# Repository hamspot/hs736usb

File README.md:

# Ham Spot Inc
##  HS-736USB
http://hamspot.com/33-prod-hs-736usb

### FT-736R to HRD USB Interface
The Yaesu FT-736R remains a popular satellite ground station transceiver.  However some modern computer software is not compatible with the CAT interface on the FT-736R.  Ham Radio Deluxe, in particular, does not support the FT-736R.  Ham Radio Deluxe does support the Yaesu FT-847 which has similar features.  We can solve this incompatibility by programming a CAT interface to present a FT-847 to the PC and emulate the new commands not supported on the FT-736R.  

Features not present on the FT-736R are ignored.  Memory channels are not supported and the radio must be set to VFO, also satellite mode must be set to VFO, before enabling CAT control of the radio.  1240 MHz is mapped to 240 MHz because the FT-847 does not have 4 MHz digits.

### Credits
A short history, archived Comcast pages, and the original downloads are in **[Archives/README.md](Archives/README.md)**.

The concept was developed by Dave, KA6BFB in 2010 (Windows VB proof of concept, virtual serial ports): [Archives/Software.md](Archives/Software.md).

The hardware version was developed by Chuck, N6BIL (PIC18F14K50, GPL source and Eagle CAD): [Archives/Hardware.md](Archives/Hardware.md).

Ham Spot Inc based the HS-736USB on their great work and thanks them immensely for their hard work on solving a challenging problem! The goal of Ham Spot Inc is that if this interface is popular we will develop similar interfaces for other older rigs which are also not supported by HRD. Specifically in mind are the FT-757GXII, FT-890 and various Icom and Kenwood radios. There will likely be firmware updates to this hardware available on the http://hamspot.com/ website in the future. If you have a PIC programmer the chip has been socketed to allow you to flash new firmware or easily replace the device. If not, there will be made available an inexpensive preprogrammed chip that you can plugin to upgrade the firmware or convert the FT-736USB to another model Yaesu rig as they become supported.

### Arduino / ATmega328P port

An Arduino Uno/Nano port of the CAT translator lives in **[Arduino/](Arduino/)**. It keeps the PIC 847↔736 mapping, adds native-736 passthrough (pin A1 or a CAT opcode), PTT/band GPIO, and an S-meter PWM. The PIC firmware in `Firmware/` is unchanged.

```
arduino-cli compile --fqbn arduino:avr:nano Arduino/firmware
cd Arduino && test/run_suite.sh
```

See `Arduino/README.md`, `Arduino/docs/WIRING.md`, and `Arduino/docs/PROTOCOLS.md`. Operating manuals for both the PIC cabinet and the Arduino port are in [`Manual/`](Manual/).

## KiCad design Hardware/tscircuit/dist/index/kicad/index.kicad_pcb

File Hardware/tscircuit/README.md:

# HS-736USB Nano carrier (tscircuit)

Arduino Nano plugs into `JP_L` / `JP_R`. This board is the I/O carrier
(CAT, PTT MOSFET, RCA sense, dialect jumper, LCD, band, PWM). The MCU
is not redrawn.

CAT DIN pin 6 (+13.8 V) is not connected. Power is Nano USB 5 V.

## CLI

IndianaDell installs tscircuit under `~/.local` (`bin/tsci` runs `node`
on `cli.mjs`). The npm shebang is bun, and node cannot load `.tsx`.

From this directory, use the project CLI with bun:

```bash
BUN=/tmp/bunpkg/node_modules/bun/bin/bun.exe
# npm install --prefix /tmp/bunpkg bun  (Linux binary is named bun.exe)

"$BUN" node_modules/tscircuit/cli.mjs check netlist
"$BUN" node_modules/tscircuit/cli.mjs check schematic-placement
"$BUN" node_modules/tscircuit/cli.mjs check placement
"$BUN" node_modules/tscircuit/cli.mjs build --pcb-svgs --schematic-svgs --kicad-project
"$BUN" node_modules/tscircuit/cli.mjs check shorts
inkscape dist/index/pcb.svg --export-type=png --export-filename=dist/index/pcb.png --export-dpi=1200
inkscape dist/index/schematic.svg --export-type=png --export-filename=dist/index/schematic.png --export-dpi=1200
```

Do not `tsci push` or order boards unless asked.

`<schematicsheet>` is omitted on purpose: with it, `kicad_sch` export
is a hierarchical stub (`main.kicad_sch` never written). Sections
still group the schematic.

Known warnings: builtin symbols missing `{REFDES}` text; SOD-123 has
no 3D model on the tscircuit CDN.

Outputs: `dist/index/pcb.png`, `dist/index/schematic.png`,
`dist/index/kicad/`.

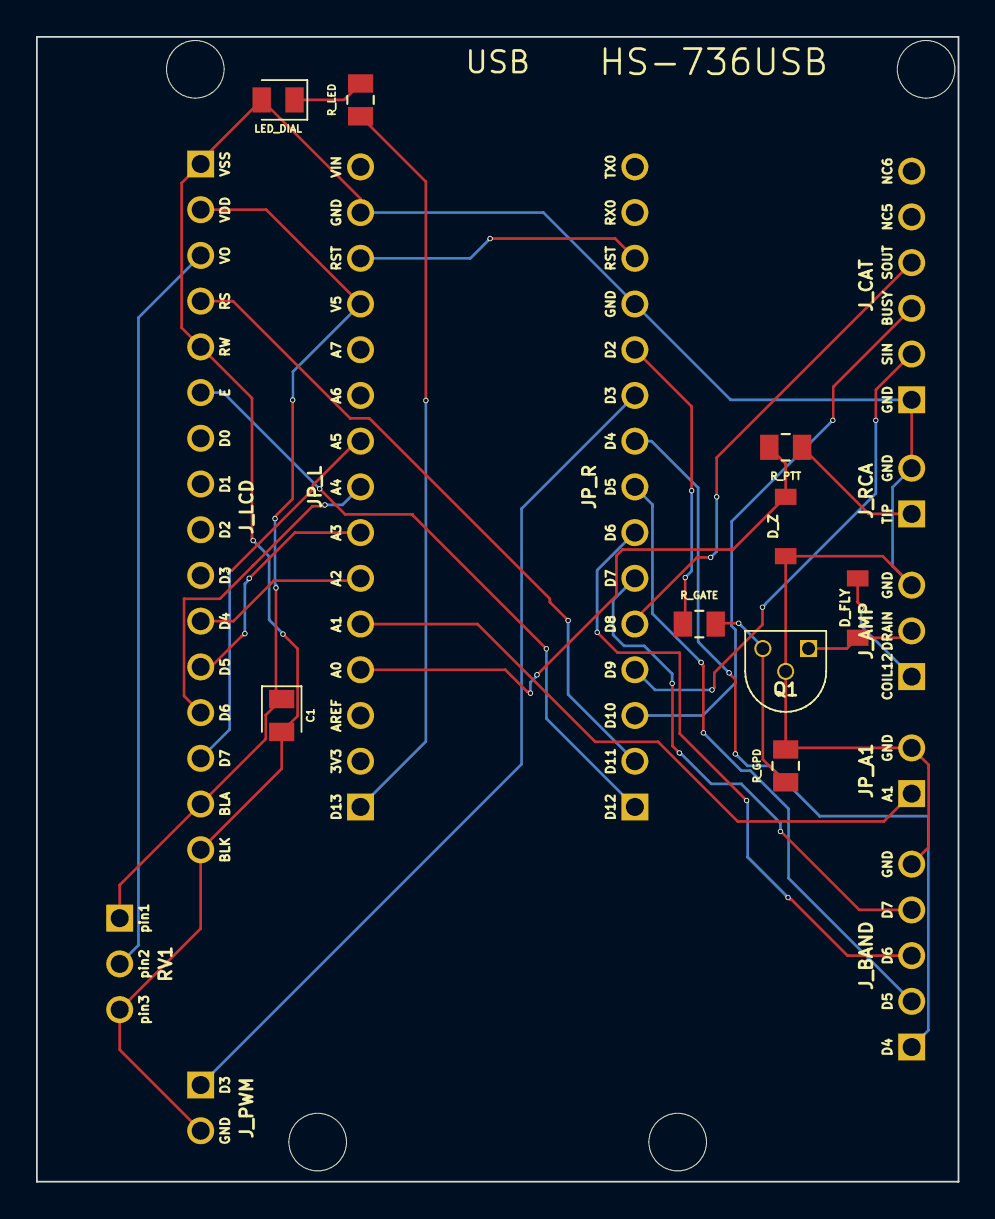
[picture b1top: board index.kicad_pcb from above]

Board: 2 copper layers, 51.2 x 63.6 mm, 19 parts (0 on the bottom side), 27 nets.

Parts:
C1: 100nF; capacitor_cap0805
D_FLY: D; diode_sod123
D_Z: D; diode_sod123
JP_A1: JP_A1; pin_header_pinrow2_p2.54
JP_L: JP_L; pin_header_pinrow15_p2.54_female
JP_R: JP_R; pin_header_pinrow15_p2.54_female
J_AMP: J_AMP; pin_header_pinrow3_p2.54
J_BAND: J_BAND; pin_header_pinrow5_p2.54
J_CAT: J_CAT; pin_header_pinrow6_p2.54_female
J_LCD: J_LCD; pin_header_pinrow16_p2.54_female
J_PWM: J_PWM; pin_header_pinrow2_p2.54
J_RCA: J_RCA; pin_header_pinrow2_p2.54_female
LED_DIAL: LED; led_0805_color(green)
Q1: Q1; mosfet_to92
RV1: 10kΩ; potentiometer_pinrow3
R_GATE: 100Ω; resistor_res0805
R_GPD: 10kΩ; resistor_res0805
R_LED: 330Ω; resistor_res0805
R_PTT: 22kΩ; resistor_res0805

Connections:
A0: D_Z.2, JP_L.4, R_PTT.2
A1: JP_A1.1, JP_L.5
A2: JP_L.6, J_LCD.11
A3: JP_L.7, J_LCD.12
A4: JP_L.8, J_LCD.13
A5: JP_L.9, J_LCD.14
BUSY: JP_R.3, J_CAT.3
COIL12: D_FLY.2, J_AMP.1
D2: JP_R.11, R_GATE.1
D3: JP_R.10, J_PWM.1
D4: JP_R.9, J_BAND.1
D5: JP_R.8, J_BAND.2
D6: JP_R.7, J_BAND.3
D7: JP_R.6, J_BAND.4
D11: JP_R.2, J_LCD.4
D12: JP_R.1, J_LCD.6
D13: JP_L.1, R_LED.1
GND: C1.2, D_Z.1, JP_A1.2, JP_L.14, JP_R.12, J_AMP.3, J_BAND.5, J_CAT.1, J_LCD.1, J_LCD.5, J_LCD.16, J_PWM.2, J_RCA.2, LED_DIAL.2, Q1.2, RV1.3, R_GPD.2
LCD_VO: J_LCD.3, RV1.2
LED_A: LED_DIAL.1, R_LED.2
PTT_SW: D_FLY.1, J_AMP.2, Q1.1
QG: Q1.3, R_GATE.2, R_GPD.1
RCA: J_RCA.1, R_PTT.1
RST: JP_L.13, JP_R.13
SIN: JP_R.4, J_CAT.2
SOUT: JP_R.5, J_CAT.4
V5: C1.1, JP_L.12, J_LCD.2, J_LCD.15, RV1.1

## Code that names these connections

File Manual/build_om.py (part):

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        P(
            "PIC cabinet: the silkscreen already reads S-IN / S-OUT / GND; "
            "those pads go to pins 2, 4 and 1. Nano carrier: plug the 6-pin "
            "DIN into <b>J_CAT</b> (GND, SIN, BUSY, SOUT, NC, NC). Pin 6 is "
            "not connected. Arduino D9 is AltSoftSerial TX, D8 is RX "
            "(Timer 1). Levels are TTL idle-high, same as the original "
            "HS-736USB. Do not insert a MAX232 unless your particular radio "
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        om_table(
            ["Carrier jack", "Pins", "Goes to"],
            [
                ["J_CAT", "GND SIN BUSY SOUT NC NC", "FT-736R CAT DIN (pin 6 open)"],
                ["J_AMP", "COIL12 DRAIN GND", "amp PTT MOSFET drain / coil +12"],
                ["J_RCA", "TIP GND", "radio PTT RCA sense (22 k + zener)"],
                ["JP_A1", "A1 GND", "open = 847 dialect; jumper = 736"],
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        P(
            "The 736 PTT RCA is 8 V open, ground-to-TX, 8 mA closed. It is "
            "in parallel with MOX and the mic PTT. <b>8 V will destroy a "
            "328 pin.</b> Y-cable the RCA: one leg still to a footswitch if "
            "you use one; the other through 22 kohm to A0, with a 5.1 V "
            "zener to GND (cathode at A0). Firmware: INPUT_PULLUP, TX = pin "
            "LOW. Unplugged = RX."
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
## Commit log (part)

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2015-02-02 Initial Import of Ham Spot HS-736USB Source Code and Hardware Design Files. Version 1.0 hardware interface.
2015-02-02 Added makercase.com cabinet plans. Dimension only. AI/SVG files will later include holes for USB, cable, LEDs, etc.
2015-02-02 Added USB status LED indicators to the schematic and board layout. Refactored the silkscreen layers to be less cluttered and within boundaries.
2016-08-18 Updated schematic and board for a small board run August 2016. Added missing Artwork for the various enclosure designs and board renderings.
2016-08-18 Moved files around to the appropriate folders.
2016-08-18 Moved renderings into appropriate folders.
2016-08-18 Updated readme for cabinet files.

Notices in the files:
Manual/build_om.py:
copyright Yaesu Musen Co., Ltd. This file is not a Yaesu publication.
